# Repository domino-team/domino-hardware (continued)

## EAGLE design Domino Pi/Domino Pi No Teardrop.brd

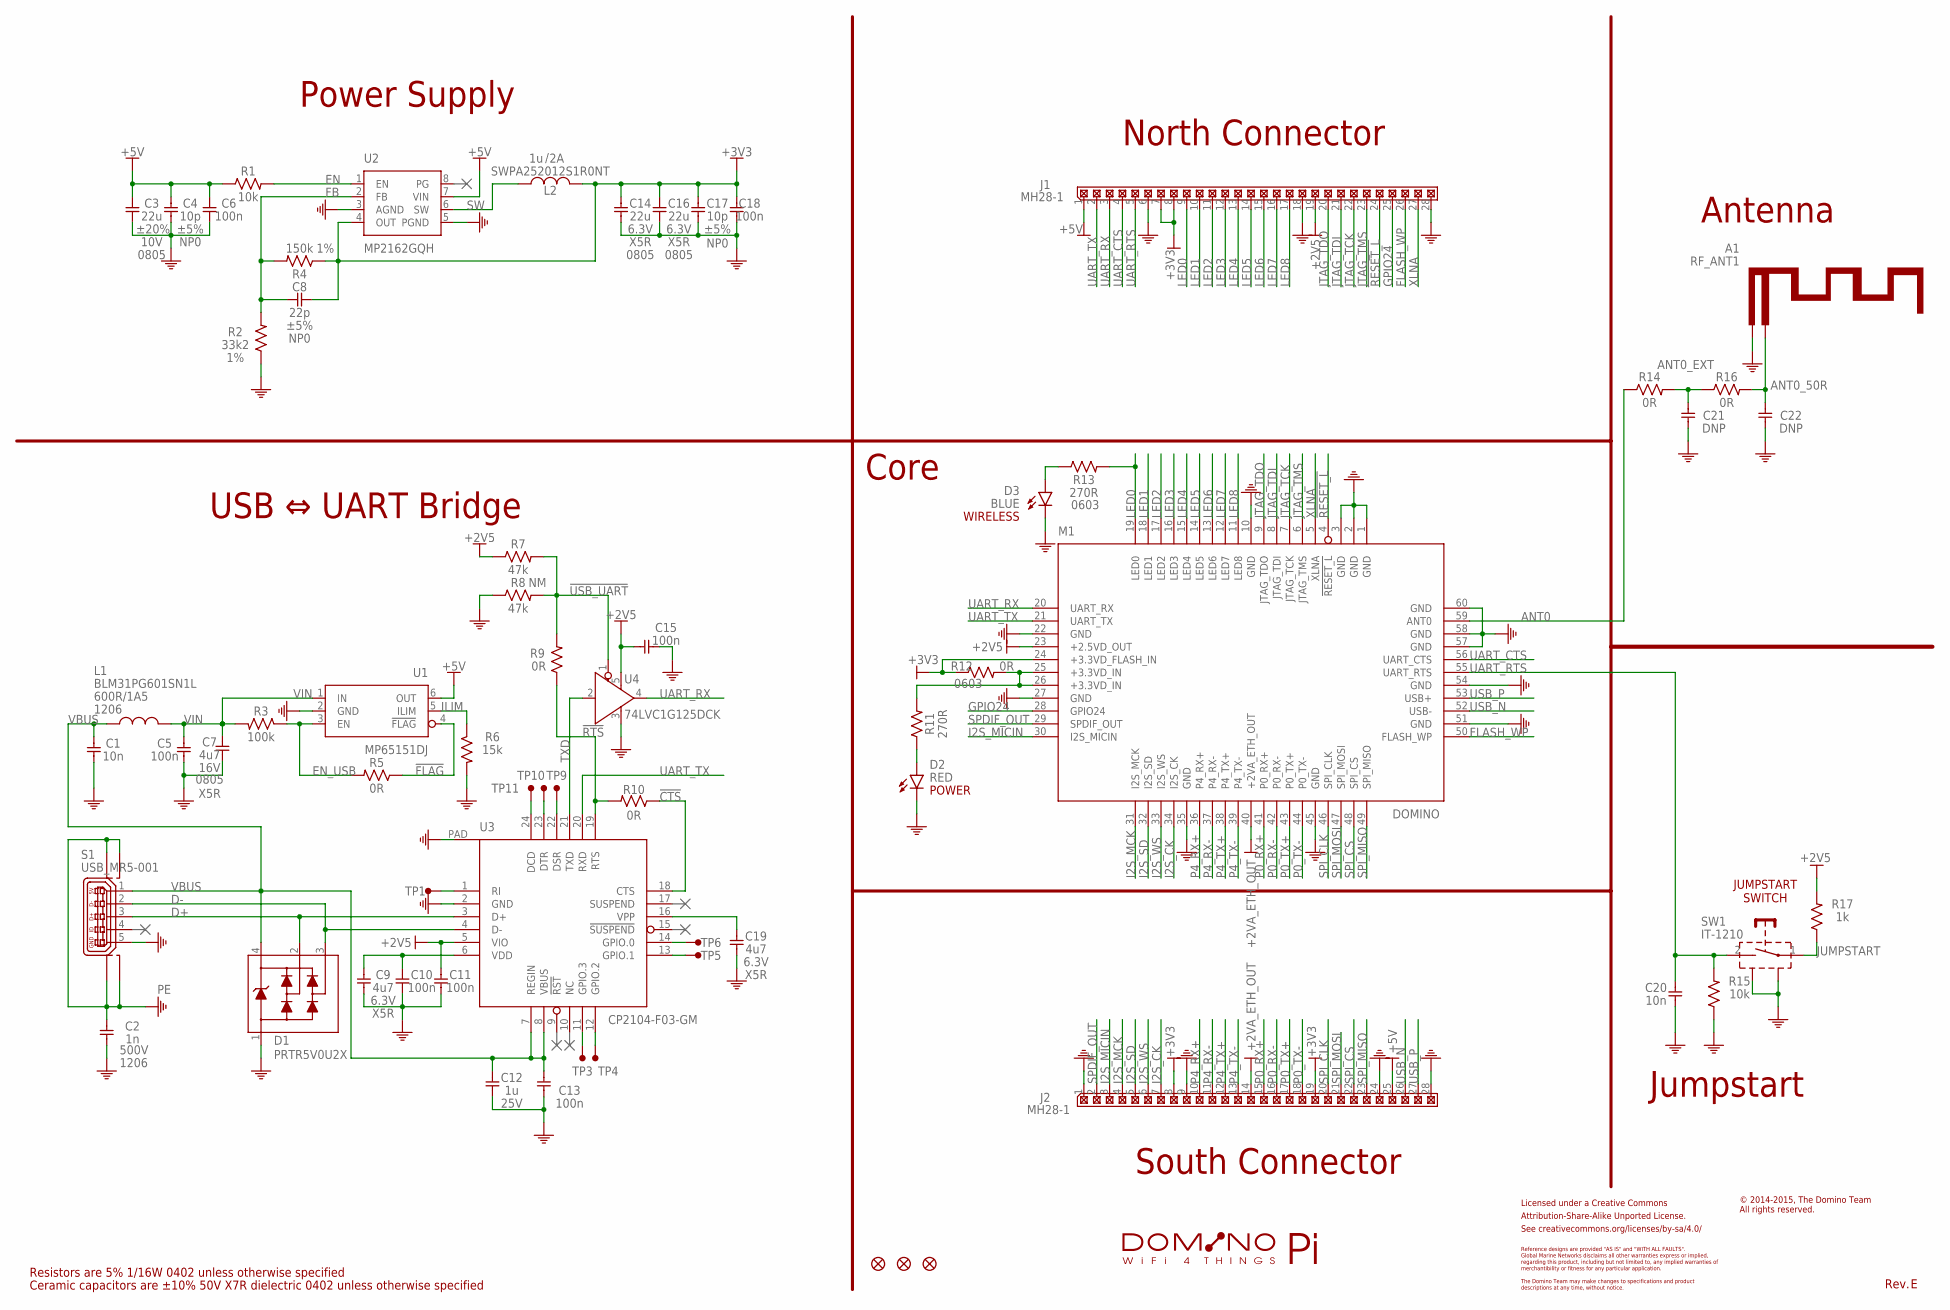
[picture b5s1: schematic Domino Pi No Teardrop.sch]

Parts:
A1: RF_ANT1; PARTNO WIFI_ANT-2.4GHz
C1, C20: 10n; C0402; PARTNO C0402_10n_X7R_10%_CER_50V
C2: 1n; C1206; PARTNO C1206_1n_X7R_10%_CER_500V
C3: 22u; C0805; PARTNO C1206_22u_X7R_20%_CER_10V
C4, C17: 10p; C0402; PARTNO C0402_10p_NP0_5%_CER_50V
C5, C6, C10, C11, C13, C15, C18: 100n; C0402; PARTNO C0402_100n_X7R_10%_CER_50V
C7: 4u7; C0805; PARTNO C0805_4u7_X5R_10%_CER_16V
C8: 22p; C0402; PARTNO C0402_22p_NP0_5%_CER_50V
C9, C19: 4u7; C0402; PARTNO C0402_4u7_X5R_10%_CER_6V3
C12: 1u; C0402; PARTNO C0402_1u_X7R_10%_CER_25V
C14, C16: 22u; C0805; PARTNO C0805_22u_X5R_20%_CER_6V3
C21, C22: DNP; C0402; PARTNO C0402_DNP
CC-BY-SA: CC-BY-SA_LOGO
D1: PRTR5V0U2X; SOT143B; PARTNO PRTR5V0U2X
D2: RED; LED0402; PARTNO LED0402-RED
D3: BLUE; LED0402; PARTNO LED0402-BLUE
F1, F2, F3: FIDUCIAL
J1, J2: MH28-1; MH28-1-0.1; PARTNO MH28-1-0.1
L1: BLM31PG601SN1L; FB1206; PARTNO BLM31PG601SN1L
L2: SWPA252012S1R0NT; SWPA252012S; PARTNO SWPA252012SMT
M1: DOMINO; PARTNO DOMINO-CORE
R1, R15: 10k; R0402; PARTNO R0402_10k_5%_62.5mW
R2: 33k2; R0402; PARTNO R0402_33k2_1%_62.5mW
R3: 100k; R0402; PARTNO R0402_100k_5%_62.5mW
R4: 150k; R0402; PARTNO R0402_150k_1%_62.5mW
R5, R9, R10, R14, R16: 0R; R0402; PARTNO R0402_0R_5%_62.5mW
R6: 15k; R0402; PARTNO R0402_15k_5%_62.5mW
R7, R8: 47k; R0402; PARTNO R0402_47k_5%_62.5mW
R11: 270R; R0402; PARTNO R0402_270R_5%_62.5mW
R12: 0R; R0603; PARTNO R0603_0R_5%_125mW
R13: 270R; R0603; PARTNO R0603_270R_5%_125mW
R17: 1k; R0402; PARTNO R0402_1k_5%_62.5mW
S1: USB_MR5-001; USB-MR5-001; PARTNO USB MR5-001
SW1: IT-1210; PARTNO IT-1210
TP1, TP3, TP4, TP5, TP6, TP9, TP10, TP11: TEST_PAD
U1: MP65151DJ; SOT23-6; PARTNO MP65151DJ
U2: MP2162GQH; QFN-8_2X1.5; PARTNO MP2162GQH
U3: CP2104-F03-GM; QFN-25_4X4; PARTNO CP2104-F03-GM
U4: 74LVC1G125DCK; SC70; PARTNO 74LVC1G125DCK
W1: DOMINO_PI_LOGO

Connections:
!CTS: R10.1, U3.18 (CTS)
!FLAG: R5.1, U1.4 (!FLAG)
!RESET_L: J1.24, M1.4 (!RESET_L)
!RTS: R9.1, R10.2, U3.19 (RTS)
!USB_UART: R7.2, R8.2, R9.2, U4.1 (!OE)
+2V5: C11.1, C15.2, J1.19, M1.23 (+2.5VD_OUT), R7.1, R17.2, U3.5 (VIO), U4.5 (VCC)
+2VA_ETH_OUT: J2.14, M1.40 (+2VA_ETH_OUT)
+3.3VD_IN: M1.25 (+3.3VD_IN), M1.26 (+3.3VD_IN), R11.2, R12.2
+3V3: C8.2, C14.1, C16.1, C17.1, C18.1, J1.7, J1.8, J2.8, J2.19, L2.2, M1.24 (+3.3VD_FLASH_IN), R4.1, R12.1, U2.4 (OUT)
+5V: C3.1, C4.1, C6.1, J1.1, J2.25, R1.1, U1.6 (OUT), U2.7 (VIN)
ANT0: M1.59 (ANT0), R14.1
ANT0_50R: A1.FEED, C22.1, R16.2
ANT0_EXT: C21.1, R14.2, R16.1
BLUE_LED: D3.2 (A), R13.1
D+: D1.2, S1.3, U3.3 (D+)
D-: D1.3, S1.2, U3.4 (D-)
EN: R1.2, U2.1 (EN)
EN_USB: R3.1, R5.2, U1.3 (EN)
FB: C8.1, R2.2, R4.2, U2.2 (FB)
FLASH_WP: J1.26, M1.50 (FLASH_WP)
GND: A1.GND, C1.2, C2.2, C3.2, C4.2, C5.2, C6.2, C7.2, C9.2, C10.2, C11.2, C12.2, C13.2, C14.2, C15.1, C16.2, C17.2, C18.2, C19.2, C20.2, C21.2, C22.2, D1.1, D2.1 (C), D3.1 (C), J1.6, J1.18, J1.28, J2.1, J2.9, J2.24, J2.28, M1.1 (GND), M1.2 (GND), M1.3 (GND), M1.10 (GND), M1.22 (GND), M1.27 (GND), M1.35 (GND), M1.45 (GND), M1.51 (GND), M1.54 (GND), M1.57 (GND), M1.58 (GND), M1.60 (GND), R2.1, R6.2, R8.1, R15.1, S1.5, SW1.SH$1, SW1.SH$2, U1.2 (GND), U2.3 (AGND), U2.5 (PGND), U3.2 (GND), U3.PAD, U4.3 (GND)
GPIO24: J1.25, M1.28 (GPIO24)
I2S_CK: J2.7, M1.34 (I2S_CK)
I2S_MCK: J2.4, M1.31 (I2S_MCK)
I2S_MICIN: J2.3, M1.30 (I2S_MICIN)
I2S_SD: J2.5, M1.32 (I2S_SD)
I2S_WS: J2.6, M1.33 (I2S_WS)
ILIM: R6.1, U1.5 (ILIM)
JTAG_TCK: J1.22, M1.7 (JTAG_TCK)
JTAG_TDI: J1.21, M1.8 (JTAG_TDI)
JTAG_TDO: J1.20, M1.9 (JTAG_TDO)
JTAG_TMS: J1.23, M1.6 (JTAG_TMS)
JUMPSTART: R17.1, SW1.1
LED0: J1.9, M1.19 (LED0), R13.2
LED1: J1.10, M1.18 (LED1)
LED2: J1.11, M1.17 (LED2)
LED3: J1.12, M1.16 (LED3)
LED4: J1.13, M1.15 (LED4)
LED5: J1.14, M1.14 (LED5)
LED6: J1.15, M1.13 (LED6)
LED7: J1.16, M1.12 (LED7)
LED8: J1.17, M1.11 (LED8)
unnamed: D2.2 (A), R11.1
unnamed: TP9.1, U3.22 (DSR)
unnamed: TP1.1, U3.1 (RI)
unnamed: TP3.1, U3.11 (GPIO.3)
unnamed: TP4.1, U3.12 (GPIO.2)
unnamed: TP10.1, U3.23 (DTR)
unnamed: TP11.1, U3.24 (DCD)
unnamed: TP6.1, U3.14 (GPIO.0)
unnamed: TP5.1, U3.13 (GPIO.1)
unnamed: C19.1, U3.16 (VPP)
P0_RX+: J2.15, M1.41 (P0_RX+)
P0_RX-: J2.16, M1.42 (P0_RX-)
P0_TX+: J2.17, M1.43 (P0_TX+)
P0_TX-: J2.18, M1.44 (P0_TX-)
P4_RX+: J2.10, M1.36 (P4_RX+)
P4_RX-: J2.11, M1.37 (P4_RX-)
P4_TX+: J2.12, M1.38 (P4_TX+)
P4_TX-: J2.13, M1.39 (P4_TX-)
PE: C2.1, S1.SH$1 (M0), S1.SH$2 (M1), S1.SH$3 (M2), S1.SH$4 (M3)
SPDIF_OUT: J2.2, M1.29 (SPDIF_OUT)
SPI_CLK: J2.20, M1.46 (SPI_CLK)
SPI_CS: J2.22, M1.48 (SPI_CS)
SPI_MISO: J2.23, M1.49 (SPI_MISO)
SPI_MOSI: J2.21, M1.47 (SPI_MOSI)
SW: L2.1, U2.6 (SW)
TXD: U3.21 (TXD), U4.2 (A)
UART_CTS: J1.4, M1.56 (UART_CTS)
UART_RTS: C20.1, J1.5, M1.55 (UART_RTS), R15.2, SW1.2
UART_RX: J1.3, M1.20 (UART_RX), U4.4 (Y)
UART_TX: J1.2, M1.21 (UART_TX), U3.20 (RXD)
USB_N: J2.26, M1.52 (USB-)
USB_P: J2.27, M1.53 (USB+)
VBUS: C1.1, C12.1, C13.1, D1.4, L1.2, S1.1, U3.7 (REGIN), U3.8 (VBUS)
VDD: C9.1, C10.1, U3.6 (VDD)
VIN: C5.1, C7.1, L1.1, R3.2, U1.1 (IN)
XLNA: J1.27, M1.5 (XLNA)

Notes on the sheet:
Power Supply
North Connector
South Connector
Antenna
Core
USB ⇔ UART Bridge
Ceramic capacitors are ±10% 50V X7R dielectric 0402 unless otherwise specified
Resistors are 5% 1/16W 0402 unless otherwise specified
Licensed under a Creative Commons
Attribution-Share-Alike Unported License.
See creativecommons.org/licenses/by-sa/4.0/
Reference designs are provided "AS IS" and "WITH ALL FAULTS".
regarding this product, including but not limited to, any implied warranties of
The Domino Team may make changes to specifications and product
Global Marine Networks disclaims all other warranties express or implied,
merchantibility or fitness for any particular application.
descriptions at any time, without notice.
© 2014-2015, The Domino Team All rights reserved.
Rev.
WIRELESS
POWER
JUMPSTART SWITCH
Jumpstart

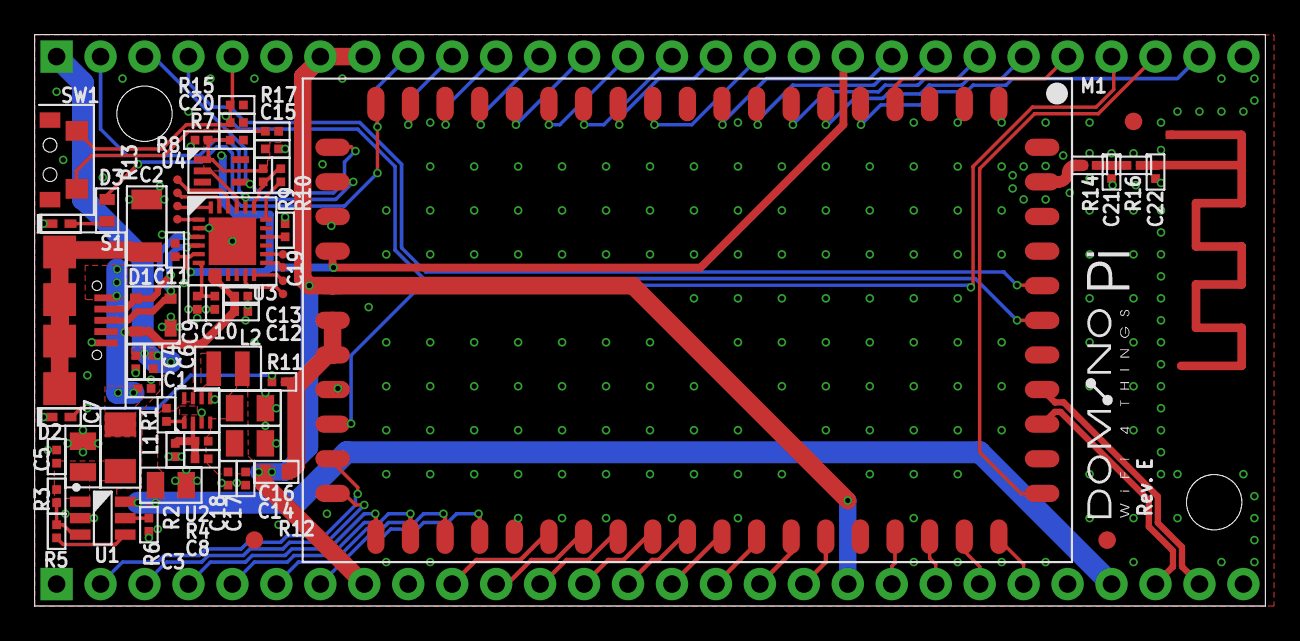
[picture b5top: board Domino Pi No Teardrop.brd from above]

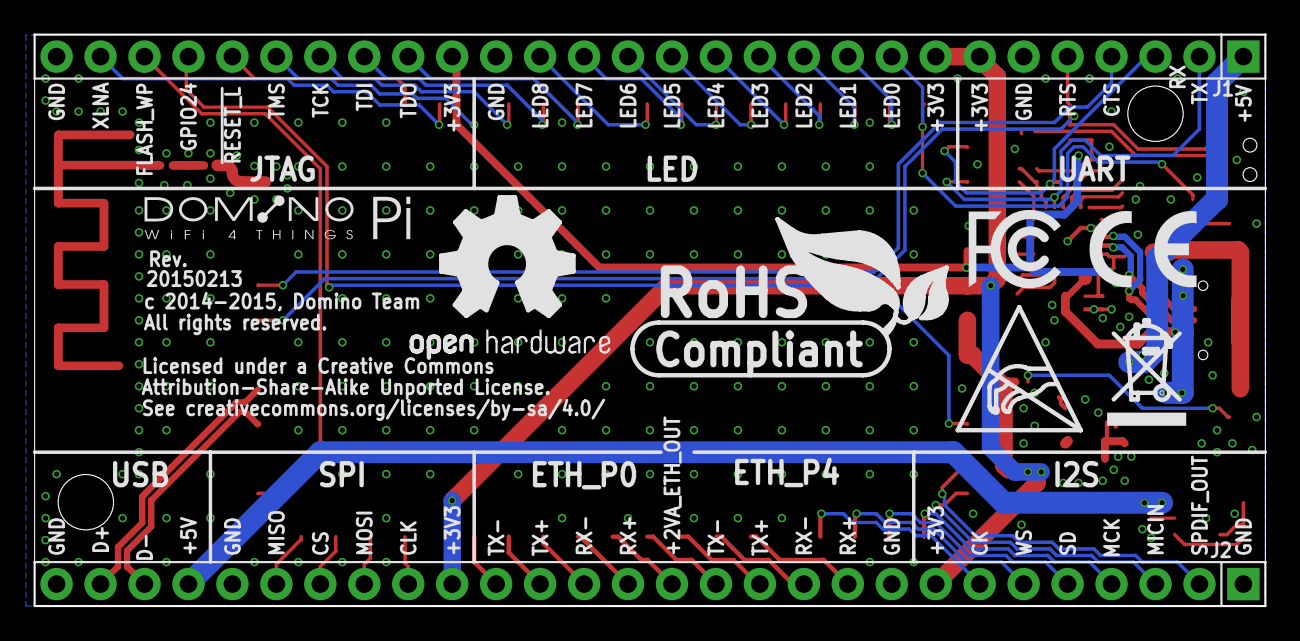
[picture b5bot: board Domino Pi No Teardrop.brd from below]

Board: 2 copper layers, 71.1 x 33.0 mm, 77 parts (9 on the bottom side), 78 nets.

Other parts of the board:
DRILEGEND: DRILEGEND
U$6, U$8: DOMINO_PI_LOGO_SMALL
U$28: A5L-LOC
U$36: ESD_LOGO
U$38: OPEN_HARDWARE_LOGO
U$39: RECYCLE_BIN_LOGO
U$40: ROHS_LOGO
U$41: CE_LOGO_SMALL
U$42: FCC_LOGO_SMALL

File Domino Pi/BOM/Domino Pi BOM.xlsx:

Item | Qty | Value | Manufacturer | Device | Package | Reference | Description | Remarks
1 | 2 | 10n | ANY | C0402_10n_X7R_10%_CER_50V | C0402 | C1, C20 | CAP CER 10000PF 50V 10% X7R 0402
2 | 1 | 1u | ANY | C0402_1u_X7R_10%_CER_25V | C0402 | C12 | CAP CER 1UF 25V 10% X7R 0402
3 | 2 | 22u | ANY | C0805_22u_X5R_20%_CER_6V3 | C0805 | C14, C16 | CAP CER 22UF 6.3V 20% X5R 0805
4 | 1 | 1n | ANY | C1206_1n_X7R_10%_CER_500V | C1206 | C2 | CAP CER 1000PF 500V 10% X7R 1206
5 | 0 | DNP | NONE | C0402_DNP | C0402 | C21(DNP), C22(DNP) | CAP DNP 0402
6 | 1 | 22u | ANY | C1206_22u_X7R_20%_CER_10V | C0805 | C3 | CAP CER 22UF 10V 20% X7R 1206
7 | 2 | 10p | ANY | C0402_10p_NP0_5%_CER_50V | C0402 | C4, C17 | CAP CER 10PF 50V 5% NP0 0402
8 | 7 | 100n | ANY | C0402_100n_X7R_10%_CER_50V | C0402 | C5, C6, C10, C11, C13, C15, C18 | CAP CER 0.1UF 50V 10% X7R 0402
9 | 1 | 4u7 | ANY | C0805_4u7_X5R_10%_CER_16V | C0805 | C7 | CAP CER 4.7UF 16V 10% X5R 0805
10 | 1 | 22p | ANY | C0402_22p_NP0_5%_CER_50V | C0402 | C8 | CAP CER 22PF 50V 5% NP0 0402
11 | 2 | 4u7 | ANY | C0402_4u7_X5R_10%_CER_6V3 | C0402 | C9, C19 | CAP CER 4.7UF 6.3V 10% X5R 0402
12 | 1 | PRTR5V0U2X | NXP | PRTR5V0U2X | SOT143B | D1 | TVS DIODE ARRAY 2CH 5V SOT143
13 | 1 | RED | ANY | LED0402-RED | LED0402 | D2 | LED RED CLEAR 0402 SMD
14 | 1 | BLUE | ANY | LED0402-BLUE | LED0402 | D3 | LED BLUE CLEAR 0402 SMD
15 | 2 | MH28-1 | ANY | MH28-1-0.1 | MH28-1-0.1 | J1, J2 | CONN HEADER VERT .100 1ROW 28POS 10.5 TAIL 8.5 BODY 15AU
16 | 1 | BLM31PG601SN1L | MURATA | BLM31PG601SN1L | FB1206 | L1 | FERRITE CHIP 600 OHM 1500MA 1206
17 | 1 | SWPA252012S1R0NT | SUNLORD | SWPA252012SMT | SWPA252012S | L2 | INDUCTOR 1.2UH 2.0A SMD2.5 X 2.0 X 1.2
18 | 1 | DOMINO | GL-CONNECT | DOMINO-CORE | DOMINO | M1 | MOD AR9331 WIFI
19 | 2 | 10k | ANY | R0402_10k_5%_62.5mW | R0402 | R1, R15 | RES 10K OHM 1/16W 5% 0402 SMD
20 | 1 | 270R | ANY | R0402_270R_5%_62.5mW | R0402 | R11 | RES 270 OHM 1/16W 5% 0402 SMD
21 | 1 | 0R | ANY | R0603_0R_5%_125mW | R0603 | R12 | RES 0.0 OHM 1/8W JUMP SMD 0603
22 | 1 | 270R | ANY | R0603_270R_5%_125mW | R0603 | R13 | RES 270 OHM 1/8W 5% 0603 SMD
23 | 1 | 1k | ANY | R0402_1k_5%_62.5mW | R0402 | R17 | RES 1K OHM 1/16W 5% 0402 SMD
24 | 1 | 33k2 | ANY | R0402_33k2_1%_62.5mW | R0402 | R2 | RES 33.2K OHM 1/16W 1% 0402 SMD
25 | 1 | 100k | ANY | R0402_100k_5%_62.5mW | R0402 | R3 | RES 100K OHM 1/16W 5% 0402 SMD
26 | 1 | 150k | ANY | R0402_150k_1%_62.5mW | R0402 | R4 | RES 150K OHM 1/16W 1% 0402 SMD
27 | 5 | 0R | ANY | R0402_0R_5%_62.5mW | R0402 | R5, R9, R10, R14, R16 | RES 0.0 OHM 1/16W JUMP 0402 SMD
28 | 1 | 15k | ANY | R0402_15k_5%_62.5mW | R0402 | R6 | RES 15K OHM 1/16W 5% 0402 SMD
29 | 1 | 47k | ANY | R0402_47k_5%_62.5mW | R0402 | R7, R8(DNP) | RES 47K OHM 1/16W 5% 0402 SMD
30 | 1 | USB_MR5-001 | SZJUSTWELL ELECTRONICS | USB MR5-001 | USB-MR5-001 | S1 | CONN USB MICRO B RECPT SMT R/A
31 | 1 | IT-1210 | SZJUSTWELL ELECTRONICS | IT-1210 | IT-1210 | SW1 | SWITCH TACTILE SPST-NO 0.05A 12V
32 | 1 | MP65151DJ | MONOLITHIC POWER | MP65151DJ | SOT23-6 | U1 | IC POWER SWITCH 1.7A SOT23-6
33 | 1 | MP2162GQH | MONOLITHIC POWER | MP2162GQH | QFN-8_2X1.5 | U2 | IC REG BUCK SYNC ADJ 2A 8WDFN
34 | 1 | CP2104-F03-GM | SILICON LABORATORIES | CP2104-F03-GM | QFN-25_4X4 | U3 | IC SGL USB-TO-UART BRIDGE 24QFN
35 | 1 | 74LVC1G125DCK | TEXAS INSTRUMENTS | 74LVC1G125DCK | SC70 | U4 | IC BUFF/DVR TRI-ST N-INV SC705

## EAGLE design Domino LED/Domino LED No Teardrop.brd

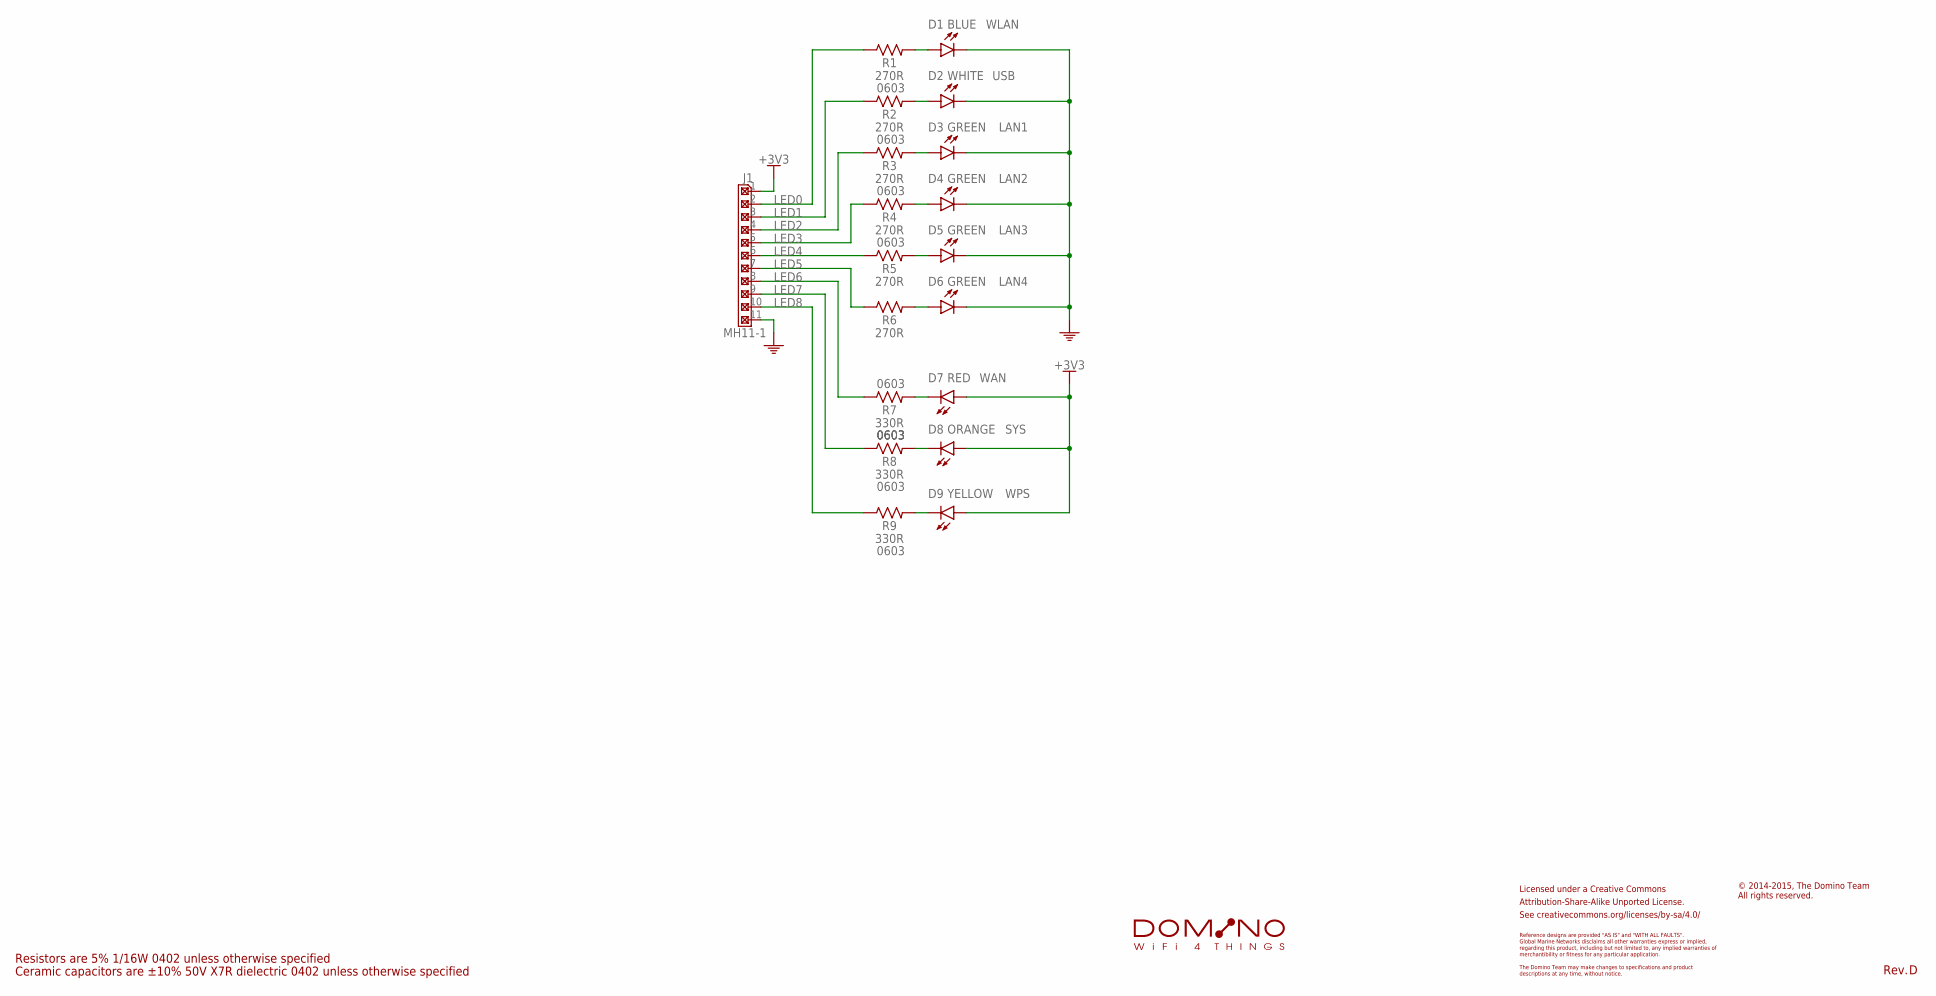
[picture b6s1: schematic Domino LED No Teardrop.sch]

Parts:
CC-BY-SA1: CC-BY-SA_LOGO
D1: BLUE; LED0603; PARTNO LED0603-BLUE
D2: WHITE; LED0603; PARTNO LED0603-WHITE
D3, D4, D5, D6: GREEN; LED0603; PARTNO LED0603-GREEN
D7: RED; LED0603; PARTNO LED0603-RED
D8: ORANGE; LED0603; PARTNO LED0603-ORANGE
D9: YELLOW; LED0603; PARTNO LED0603-YELLOW
J1: MH11-1; MH11-1-0.1; PARTNO MH11-1-0.1
R1, R2, R3, R4, R5, R6: 270R; R0603; PARTNO R0603_270R_5%_125mW
R7, R8, R9: 330R; R0603; PARTNO R0603_330R_5%_125mW
U$4: DOMINO_LOGO

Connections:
+3V3: D7.2 (A), D8.2 (A), D9.2 (A), J1.1
GND: D1.1 (C), D2.1 (C), D3.1 (C), D4.1 (C), D5.1 (C), D6.1 (C), J1.11
LED0: J1.2, R1.1
LED1: J1.3, R2.1
LED2: J1.4, R3.1
LED3: J1.5, R4.1
LED4: J1.6, R5.1
LED5: J1.7, R6.1
LED6: J1.8, R7.1
LED7: J1.9, R8.1
LED8: J1.10, R9.1
unnamed: D1.2 (A), R1.2
unnamed: D2.2 (A), R2.2
unnamed: D3.2 (A), R3.2
unnamed: D4.2 (A), R4.2
unnamed: D5.2 (A), R5.2
unnamed: D7.1 (C), R7.2
unnamed: D8.1 (C), R8.2
unnamed: D9.1 (C), R9.2
unnamed: D6.2 (A), R6.2

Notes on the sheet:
Ceramic capacitors are ±10% 50V X7R dielectric 0402 unless otherwise specified
Resistors are 5% 1/16W 0402 unless otherwise specified
Licensed under a Creative Commons
Attribution-Share-Alike Unported License.
See creativecommons.org/licenses/by-sa/4.0/
Reference designs are provided "AS IS" and "WITH ALL FAULTS".
regarding this product, including but not limited to, any implied warranties of
The Domino Team may make changes to specifications and product
Global Marine Networks disclaims all other warranties express or implied,
merchantibility or fitness for any particular application.
descriptions at any time, without notice.
© 2014-2015, The Domino Team All rights reserved.
Rev.
WLAN
USB
LAN1
LAN2
LAN3
LAN4
WAN
SYS
WPS

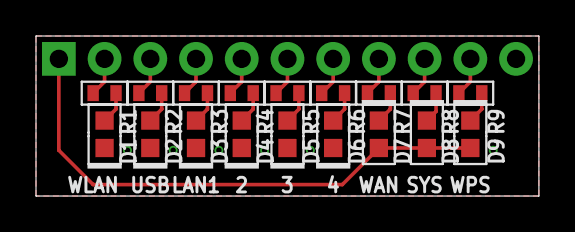
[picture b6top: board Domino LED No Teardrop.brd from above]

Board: 2 copper layers, 27.9 x 8.9 mm, 23 parts (1 on the bottom side), 20 nets.

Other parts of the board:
DRILEGEND: DRILEGEND
U$3: A5L-LOC

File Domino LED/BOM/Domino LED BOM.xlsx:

Item | Qty | Value | Manufacturer | Device | Package | Reference | Description | Remarks
1 | 1 | BLUE | ANY | LED0603-BLUE | LED0603 | D1 | LED BLUE CLEAR 0603 SMD
2 | 1 | WHITE | ANY | LED0603-WHITE | LED0603 | D2 | LED WHITE CLEAR 0603 SMD
3 | 4 | GREEN | ANY | LED0603-GREEN | LED0603 | D3, D4, D5, D6 | LED GREEN CLEAR 0603 SMD
4 | 1 | RED | ANY | LED0603-RED | LED0603 | D7 | LED RED CLEAR 0603 SMD
5 | 1 | ORANGE | ANY | LED0603-ORANGE | LED0603 | D8 | LED ORANGE CLEAR 0603 SMD
6 | 1 | YELLOW | ANY | LED0603-YELLOW | LED0603 | D9 | LED YELLOW CLEAR 0603 SMD
7 | 1 | MH11-1 | ANY | MH11-1-0.1 | MH11-1-0.1 | J1 | CONN HEADER VERT .100 1ROW 11POS 8.08 HEAD 3.05 TAIL 15AU
8 | 6 | 270R | ANY | R0603_270R_5%_125mW | R0603 | R1, R2, R3, R4, R5, R6 | RES 270 OHM 1/8W 5% 0603 SMD
9 | 3 | 330R | ANY | R0603_330R_5%_125mW | R0603 | R7, R8, R9 | RES 330 OHM 1/8W 5% 0603 SMD

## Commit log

2014-08-10 Changed directory organization for revision B
2014-08-10 Point to common part database for BOM
2014-08-10 Remvoed references to other projects
2014-08-10 Cleanup
2014-08-10 Changed copyright
2014-08-12 Created Domino Single Ethernet Revision B and updated Domino LED tiles
2014-08-12 ... and all the files I missed
2014-08-13 Made Single Ethernet tile with component on top side only
2014-08-15 Domino tile Dual Ethernet Revision B
2014-08-17 Domino Single USB tile Revision B
2014-08-17 Added M3 hole to Domino Single USB tile
2014-08-17 Added M3 hole dimensions to Domino Single USB tile
2014-08-18 Re-routed Single USB tile to remove vias on USB traces
2014-08-20 Replaced RJ45 Jack with one model without LED in Dual Ethernet tile
2014-08-21 Domino Single Ethernet tile Revision B
2014-08-21 Domino Pi Dual Ethernet tile: Removed thermals on copper pour and completed pinout
2014-08-22 Domino JTAG/SPI tile Revision B
2014-08-24 Modified Domino Flash SPI tile to fit a standard SPI Flash jig and SPI Flash chip footprint
2014-08-24 Added series resistors on SPI Flash SO in Domino JTAG SPI tile
2014-08-27 Added vias to JTAG SPI tile for better RF performance
2014-09-30 Added new right tile layout for Domino USB MicroSD
2014-10-10 Added first Domino Qi Mini board
2014-12-15 Changed Domino JTAG SPI to Rev. C
2014-12-30 Domino Pi rev. C: removed Schottky diode on +VUSB, it causes too much voltage drop, optimized power wiring, changed Logos
2014-12-30 Domino JTAG SPI Rev. C: changed Logos
2014-12-30 Domino LED Rev. C: changed Logos
2014-12-30 Domino Single Ethernet Rev. C: changed Logos
2014-12-30 Domino Single USB Rev. C: changed Logos
2014-12-30 Domino Qi Mini: work in progress
2014-12-31 Domino Dual Ethernet Rev. C: Changed dual Magjack connector for new one, changed Logos
2014-12-31 Domino Single USB Rev. C: removed the resetable fuse that causes too much drop for high-current USB devices
2015-01-06 Work in progress: changed for PCB antenna and removed Schottky diode on Domino Qi Mini, first Domino Qi draft
2015-01-06 Pushed remaining Domino Qi files
2015-01-16 Added USB power switch to Sinfle USB tile
2015-01-17 Domino Single USB tile Rev. D: added resistors en power siwtch feedback and enable, changed output capacitor to smaller one
2015-01-19 Domino Pi Rev. D: replaced resetable fuse by power swich, mino changes DC/DC layout and added more stitching vias
2015-01-19 Domino Pi Rev. D: added some vias, spaced antenna pi network components and removed solder paste from antenna
2015-01-19 Domino Pi Rev. D: bumped year in bottom silkscreen
2015-01-19 Domino Pi Rev.D: removed some leftover traces within poured areas
2015-01-20 Work in progress on Domino Qi Mini board
2015-01-20 Domino Pi Rev.D: removed silkscreen for test pads, moved text to make them nicer
2015-01-26 Work in progress on Domino Qi Mini board: clustered all voltage translator chips instead of putting them close to ATMega32U4
2015-01-27 Domino Qi Mini: only 20 airwires left
2015-01-27 Domino Qi Mini: Work in progress, only 8 airwires left
2015-01-28 Domino Qi Mini: only 1 airwire left!
2015-01-29 Domino Qi Mini rev. A: eventually no more airwires
2015-01-30 Domino Qi Mini Rev. A: changes in bottom silkscreen
2015-01-31 Domino Qi Mini Rev. A: added BOM and a few datasheets
2015-02-03 Domino I2S Rev. A: work in progress
2015-02-04 Domino I2S Rev. A: added mounting hole and silkscreen artwork
2015-02-07 Domino I2S Rev. A: started again from correct PADS files
2015-02-09 Domino I2S tile Rev. A: corrected ferrite beads to HH-1T2012-601
2015-02-09 Domino I2S tile Rev. B: made board multiple of 100 mils Cleaned up silkscreen made +5V trace wider Aligned some components
2015-02-12 Domino Qi Mini Rev. B: changed silkscreen font ratio to 20%
2015-02-12 Domino Dual Ethernet Rev. D: changed silkscreen font ratio to 20%
2015-02-12 Domino I2S Rev. C: changed silkscreen font ratio to 20%
2015-02-12 Domino JTAG SPI Rev. D: changed silkscreen font ratio to 20%
2015-02-13 Domino LED Rev. D: changed silkscreen font ratio to 20%
2015-02-13 Domnio Pi Rev. E: changed silkscreen font ratio to 20%
2015-02-13 Domnio Single Ethernet Rev. D: changed silkscreen font ratio to 20%
2015-02-13 Domino Single USB Rev. E: changed silkscreen font ratio to 20%
2015-03-06 Domino Qi Mini Rev. C: changed NTB0102GU to NTB0102GF
2015-03-18 Domino Qi Mini Rev. D: corrected bridge pinout
2015-04-10 Added Inkscape pinout source files
2015-04-10 Inverted OC4A function on ping PC6 in Domino Qi pinout
2015-04-19 Added Domino Di Rev. A board
2015-04-20 Domino Di Rev. A: added slider switch
2015-05-09 Added UART header to both Ethernet tiles
2015-05-09 Changed Domino Qi Mini to 4 layers
2015-05-10 Domino Di Rev. B: removed battery charger as too complex
